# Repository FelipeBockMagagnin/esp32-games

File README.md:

# dotcompany Games

Every game for the dotcompany board (ESP32, 240x320 ILI9341, five buttons, a buzzer), the menu
that switches between them, the board's PCB and case, and the site that installs them over USB
from the browser (Chrome or Edge, through Web Serial and
[ESP Web Tools](https://esphome.github.io/esp-web-tools/)), served by GitHub Pages from `docs/`.

```
games/<id>/       one PlatformIO project per game, plus its game.json and screen.png
games/categories.json   the site's shelves, in page order
launcher/         the menu that boots the chosen game when several share a board
lib/              the engine the games share: dotcore (buttons, backlight, saves, settings,
                  pitches.h, Launcher.h) and dotui (the UI elements)
common.ini        the board's PlatformIO config, read by every platformio.ini
hardware/         the carrier PCB and the printed case
docs/             the site
tools/            publish.py, make_mockups.py, make_brand.py
```

## Publish

```bash
tools/publish.py              # every game whose firmware changed since it was published
tools/publish.py idle pet     # just these (`launcher` for the menu)
tools/publish.py --all        # everything
tools/publish.py --list       # only the game list and the screens, building nothing
git add docs && git commit -m "publish firmware" && git push
```

A game's version is the last commit that touched its firmware (its `src/`, `include/`, `lib/`
and `platformio.ini`, plus the repo's `lib/` and `common.ini`), so editing a description or another game
rebuilds nothing. Each build starts from clean. The script refuses a game with uncommitted
changes, so a published version is always a commit, and one with git-ignored files under `src/`
or `include/` (the Pomodoro's `secrets.h` holds a WiFi password, which must never reach a public
firmware). It writes `docs/firmware/<id>/` (the four images, the manifest, the launcher's icon)
and `docs/games.js`, and drops what is left of a game whose folder is gone.

The images keep their own offsets (bootloader 0x1000, partitions 0x8000, boot_app0 0xE000,
app 0x10000) instead of one merged image, whose 0xFF padding would cover NVS at 0x9000 and
erase every game's save. Every game must keep the default partition table for that to hold.

## Add a game

1. Copy the closest game to `games/<id>/`. The folder name is the id the site and the launcher use.
2. Give it its own NVS namespace, and make its reset clear only that namespace.
3. Write `game.json`:
   - `name`, `tagline`, `category` (an `id` from `games/categories.json`), `description` and `accent`;
   - optionally `order` (its place on the page and in the menu; unset goes last), `env`
     (default `esp32dev`) and `icon` (`[x, y, factor]`: the 64x64 icon the launcher and the site
     show is a crop of the screen, `64 * factor` wide).
4. Add a 240x320 `screen.png` (`tools/make_mockups.py` draws the existing games').
5. Commit, then run `tools/publish.py`. The site picks the game up from its folder.

## The console

The console on the page is the printed case: its proportions, window and D-pad come from
`hardware/case/case.scad`, measured in `--mm` (5.5556px, so the display's 43.2mm come out at its
240 pixels). `tools/make_brand.py` draws the engraved wordmark, the back's character and the
favicons from `hardware/case/brand.scad`. Rerun it if the case art changes.

## Preview

```bash
python3 -m http.server -d docs 8000   # http://localhost:8000, a secure context like HTTPS
```

## GitHub Pages

Settings → Pages → Deploy from a branch → `main`, folder `/docs`.

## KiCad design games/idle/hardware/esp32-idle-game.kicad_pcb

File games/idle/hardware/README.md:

# Placa do ESP32 Idle Game (v5)

Placa portátil de **62×100 mm**, 2 camadas, só com componentes PTH (fáceis de soldar à mão). Cabe na faixa mais barata da JLCPCB (US$ 2 por 5 placas).

- **Frente:** display de 2.8" no alto e a cruz de botões embaixo. OK fica no meio, UP em cima, DOWN embaixo, LEFT (tela anterior) à esquerda e RIGHT (próxima tela) à direita.
- **Verso:** a ESP32 deitada atrás do display, com o USB saindo pela lateral esquerda (vista de frente). Logo abaixo dela ficam o buzzer, R1, Q1, D1 e C1.

**O display de 2.8" não cabe inteiro numa placa de 100 mm** acima dos botões. Por isso o conector dele fica na borda de baixo do módulo, logo acima da cruz, e os ~17 mm de cima passam da borda da placa, apoiados em trilhos da case. Assim a PCB continua na faixa de US$ 2.

**O display e a ESP32 vão soldados direto na placa**, sem soquete. Isso deixa a case com **23 mm** de espessura, mas para tirar um deles depois é preciso dessoldar.

| Frente | Verso (visto por trás) |
|---|---|
|  |  |

## Arquivos

- `fab/esp32-idle-game-gerbers.zip`: o arquivo que se envia para a fábrica.
- `esp32-idle-game.kicad_pcb`: a placa, que abre no KiCad 10.
- `bom.csv`: lista de componentes por referência.
- `generate_pcb.py` e `build.sh`: geram tudo do zero (posicionamento, roteamento com Freerouting, plano de terra, DRC, Gerbers e prévias). Mudanças se fazem no `.py`, não no KiCad.
- `viewer.html`: visualização 3D de como display, ESP32, peças, parafusos e case se encaixam, com vista explodida, corte e checagem de folgas. Abre direto no navegador (precisa de internet para carregar o Three.js). O `build.sh` atualiza os dados dela via `viewer.py`.
- `case/`: a case impressa em 3D (seção 7).

```bash
hardware/build.sh ~/Downloads/freerouting-2.5.0.jar   # requer kicad 10 e java
```

## 1. Fabricar a PCB

**JLCPCB:** https://cart.jlcpcb.com/quote

1. Clique em **Add gerber file** e envie `fab/esp32-idle-game-gerbers.zip`. O tamanho de 62×100 mm é lido sozinho.
2. Deixe o padrão: FR-4, **2 layers**, **5 unidades**, espessura 1.6 mm, HASL. A cor verde é a mais barata e a mais rápida.
3. Não marque **PCB Assembly**: a montagem é manual.
4. No frete, escolha o mais barato que tenha rastreio (Global Standard Direct ou similar).

A JLCPCB imprime um número de pedido na serigrafia. Para tirar, escolha "Remove Mark" (custa um pouco a mais).

Alternativas: **PCBWay** (https://www.pcbway.com/orderonline.aspx), com as mesmas opções, ou a **PCB Brasil** (https://pcbbrasil.com.br/prototipos), que fabrica aqui e não paga importação.

A placa chega em 1 a 3 semanas. A importação de PCB paga imposto de importação mais ICMS sobre placa e frete.

## 2. Lista de compras (uma unidade)

Duas listas com tudo o que entra numa unidade montada: uma comprando só no Brasil, outra só no exterior. Os preços são estimativas de out/2026, com dólar a R$ 5,50. Os links levam a buscas ou a produtos de referência; confira as medidas no anúncio antes de comprar.

### Comprando no Brasil

| Qtd | Item | Onde | ~R$ |
|---|---|---|---|
| 1 | ESP32 DevKit V1, **30 pinos** | [Mercado Livre](https://lista.mercadolivre.com.br/esp32-30-pinos) | 33 – 60 |
| 1 | Display TFT **2.8"** ILI9341 SPI (14 pinos, com ou sem touch) | [Mercado Livre](https://lista.mercadolivre.com.br/display-tft-ili9341) | 64 – 93 |
| 5 | Chave táctil 6×6×5 mm (vendida por unidade) | [Eletrogate](https://www.eletrogate.com/push-button-chave-tactil-6x6x5mm) | 0,75 |
| 1 | Buzzer passivo **12 mm**, 5 V (12×10 mm; pernas a 6,5 ou 7,6 mm) | [Eletrogate](https://www.eletrogate.com/buzzer-passivo-5v) | 1,90 |
| 1 | Transistor S8050 ou 2N2222A, **ou BC337 girado** (veja abaixo) | [Mercado Livre](https://lista.mercadolivre.com.br/transistor-s8050) · [Eletrogate BC337](https://www.eletrogate.com/transistor-npn-bc337) | 0,30 – 1 |
| 1 pct | Diodo 1N4148 (10 un.) | [Eletrogate](https://www.eletrogate.com/diodo-1n4148) | 1,40 |
| 1 pct | Resistor 1 kΩ 1/4 W (10 un.) | [Eletrogate](https://www.eletrogate.com/resistor-1k-1-4w-10-unidades) | 0,70 |
| 1 | Capacitor eletrolítico 100 µF, 16 ou 25 V | [Eletrogate (25 V)](https://www.eletrogate.com/capacitor-eletrolitico-100uf-x-25v) | 0,30 |
| 4 | Parafuso M3×6 | [Mercado Livre](https://lista.mercadolivre.com.br/parafuso-m3x6) | 2 – 5 |
| *opc.* | Fita kapton, se o slot SD do display encostar nos pinos do J2 | [Mercado Livre](https://lista.mercadolivre.com.br/fita-kapton) | 8 – 15 |
| *opc.* | Capacitor 10 µF 16 V, se a gravação falhar com a case fechada (entre EN e GND) | [Eletrogate](https://www.eletrogate.com/capacitor-eletrolitico-10uf-x-16v) | 0,20 |
| 1 | PCB 62×100 mm, 2 camadas (lote de 5) | [PCB Brasil](https://pcbbrasil.com.br/prototipos) (cotação online com o zip) | a cotar |
| ~50 g | Filamento PLA para a case | Se já tiver impressora | 5 – 8 |
| — | Frete de 2 a 3 lojas | | 30 – 60 |
| | **Total, sem a PCB** | | **~140 – 230 (típico ~165)** |

O display de 2.8" é fácil de achar no Brasil, o que deixa a compra nacional mais em conta do que com a tela de 2.2".

**Na Eletrogate** (estoque conferido em 07/10/2026) dá para comprar os componentes pequenos e o buzzer, mas não os módulos:

- **ESP32:** a de 30 pinos está esgotada, e a página informa 25,5 mm de largura, o que sugere fileiras a 22,86 mm, que não encaixam.
- **Display:** não vendem o 2.8" SPI.

**BC337 no lugar do S8050:** o S8050 e o 2N2222 estavam esgotados. O BC337 serve, mas a ordem das pernas dele é C-B-E, invertida em relação à placa. Monte-o **girado 180°**, com a face plana para o lado oposto ao desenho da serigrafia, para que cada perna caia no furo E, B ou C certo.

Não encontrei preço publicado da PCB Brasil. Para comparar, envie `fab/esp32-idle-game-gerbers.zip` na cotação. Se der menos de uns R$ 140 pelas 5 placas entregues, sai mais barato que a JLCPCB.

### Comprando no exterior (AliExpress + JLCPCB)

| Qtd | Item | Busca | ~US$ |
|---|---|---|---|
| 1 | ESP32 DevKit V1, **30 pinos** | [AliExpress](https://www.aliexpress.com/w/wholesale-esp32-devkit-v1-30pin.html) | 3 |
| 1 | Display TFT **2.8"** ILI9341 SPI (14 pinos, 50×86 mm) | [AliExpress](https://www.aliexpress.com/w/wholesale-2.8-tft-lcd-ili9341.html) | 6 |
| 1 pct | Chave táctil 6×6×5 mm | [AliExpress](https://www.aliexpress.com/w/wholesale-tactile-switch-6x6x5mm.html) | 1 |
| 1 pct | Buzzer passivo 12 mm, 5 V (12×9,5 ou 12×10 mm) | [AliExpress](https://www.aliexpress.com/w/wholesale-passive-buzzer-12mm-5v.html) | 1 |
| 1 pct | Transistor S8050, TO-92 | [AliExpress](https://www.aliexpress.com/w/wholesale-s8050-to-92-transistor.html) | 1 |
| 1 pct | Diodo 1N4148 | [AliExpress](https://www.aliexpress.com/w/wholesale-1n4148-diode.html) | 0,5 |
| 1 pct | Resistor 1 kΩ 1/4 W | [AliExpress](https://www.aliexpress.com/w/wholesale-resistor-1k-1%2F4w.html) | 0,5 |
| 1 pct | Capacitor eletrolítico 100 µF 16 V, 5×11 mm | [AliExpress](https://www.aliexpress.com/w/wholesale-electrolytic-capacitor-100uf-16v-5x11.html) | 0,5 |
| 1 pct | Parafuso M3×6 | [AliExpress](https://www.aliexpress.com/w/wholesale-m3x6-screw.html) | 1 |
| | AliExpress, subtotal | | 14,50 |
| | + ICMS (pedido até US$ 50, Remessa Conforme) | | ≈ 18,10 → **R$ 100** |
| 5 | PCB 62×100 mm (JLCPCB), US$ 2 + frete Global Standard ~US$ 11 | [JLCPCB](https://cart.jlcpcb.com/quote) | 13 |
| | + imposto de importação 60% e ICMS | | ≈ 26 → **R$ 143** |
| ~50 g | Filamento PLA para a case | | R$ 5 – 8 |
| | **Total** | | **~R$ 250** |

No exterior, os pacotes de peças pequenas e as 4 PCBs que sobram já dão para montar mais unidades. A segunda unidade custa só a ESP32 e o display, uns R$ 60 a mais.

### Qual compensa

- **Uma unidade:** no Brasil, as peças dão uns R$ 165 com frete, mais a cotação da PCB Brasil. No exterior, sai tudo por uns R$ 250, com 3 a 6 semanas de espera. Para uma unidade, comprar as peças aqui costuma ganhar.
- **Duas ou mais unidades:** o exterior ganha. As peças são muito mais baratas e a PCB já vem em lote de 5.

## 3. Ferramentas

- Ferro de solda (ponta fina, ~330 °C) e estanho 0,8 mm com fluxo
- **Alicate de corte rente** (indispensável: vários terminais precisam ficar rentes à placa)
- Multímetro (para o teste de continuidade)
- Fita crepe ou massinha, para segurar as peças enquanto solda

## 4. Montagem

A regra geral: **cada peça entra pelo lado em que fica e é soldada pelo lado oposto.**

O display fica a só 2,5 mm da frente da placa, e a ESP32 a 2,5 mm do verso. Por isso, **todo terminal soldado embaixo deles precisa ser cortado rente**, a menos de 1 mm. E a ordem importa: a ESP32 vem antes do display, porque a solda dela fica escondida embaixo do display.

### Antes de começar: confira
1. **Ordem dos pinos do display.** Acima do J1, na frente da placa, estão impressos os nomes dos 14 pinos (VCC, GND, CS… T_IRQ). Com o display de face para cima e o conector embaixo, o VCC fica à **esquerda** (conferido num módulo real). Compare com a marcação do seu módulo. Se estiver espelhado, **não solde**: troque o lado do pino 1 do J1 no `generate_pcb.py` (`display_left` e o ângulo do footprint) e gere a placa de novo.
2. **Largura da ESP32.** Meça a distância entre as duas fileiras de pinos, centro a centro. Precisa dar 25,4 mm.
3. **A ESP32 funciona?** Ligue-a no USB e grave o jogo (seção 6) antes de soldar. Depois de soldada, trocar dá trabalho.

### Verso (lado azul na prévia): componentes abaixo da ESP32
4. **R1 (1 kΩ):** dobre as pernas, encaixe pelo verso e solde pela frente. Não tem polaridade.
5. **D1 (1N4148):** a faixa preta do diodo vai do lado marcado **K**.
6. **Q1 (S8050):** as pernas seguem as letras **E B C** impressas. Empurre até o corpo ficar a ~1 mm da placa. Um BC337 (pernas C-B-E) entra girado 180°, com a face plana para o lado oposto ao desenho.
7. **Buzzer:** a perna **+** vai no pad quadrado (marcado com +). Os furos são oblongos: servem para pernas a 6,5 ou 7,6 mm. Encostado na placa. Com 10 mm de altura, é a peça mais baixa do verso: a case fica 1 mm abaixo dele.
8. **C1 (100 µF):** a perna longa (+) vai no pad marcado com **+**. Dobre as pernas a 90° rente ao corpo e deite o capacitor sobre o retângulo "C1" impresso, na direção dos botões.
9. Corte rente, na frente, as pernas de todos eles: essa área fica embaixo do display.

### Frente (lado vermelho na prévia)
10. **Botões:** os cinco encaixam por pressão. Solde as 4 pernas de cada um, conferindo se ficaram rentes à placa.

### Teste antes dos módulos
11. Com o multímetro em continuidade, meça entre os pads **VIN** e **GND** do J3 (verso). **Não pode apitar.** Se apitar, há um curto: procure uma ponte de solda.
12. Aperte cada botão e meça entre o pad dele no J2/J3 (D19, D22, D27, D26 e D23) e o GND. Deve apitar só enquanto o botão estiver apertado.

### ESP32 (verso)
13. Encaixe os pinos da ESP32 pelo **verso**, deitada, **com os componentes virados para fora e o USB voltado para a borda esquerda** (vista pela frente; pelo verso, fica à direita, onde está escrito "USB"). O espaçador plástico dos pinos deve encostar na placa.
14. Solde pela frente: primeiro um pino de cada ponta, confira se ficou reta, depois o resto.
15. **Corte rente todos os 30 pinos na frente.** Eles ficam embaixo do display.

### Display (frente)
16. Encaixe os 14 pinos do display pela **frente**, de face para cima e **com o conector embaixo**, perto dos botões. O espaçador plástico deve encostar na placa, e o resto do módulo passa da borda de cima.
17. Solde pelo verso, logo acima dos botões, e corte as pontas. Até a placa entrar na case, segure o display com cuidado: a parte que passa da placa fica sem apoio.

### Acabamento
18. Monte na case (seção 7) ou, sem case, parafuse 4 espaçadores M3 de 12 mm no verso como pés.

## 5. Primeiro teste

Ligue o USB. O LED vermelho da ESP32 deve acender, o display deve mostrar o jogo e o buzzer deve tocar ao apertar RIGHT.

Se a tela ficar branca, confira as soldas do display. Se nada acender, desligue e refaça o teste de VIN e GND.

## 6. Gravar o jogo

Com a ESP32 conectada ao computador:

```bash
~/.platformio/penv/bin/pio run -t upload
```

O display de 2.8" usa o mesmo controlador (ILI9341) e a mesma resolução, então a configuração não muda. Como o conector fica embaixo, a imagem pode aparecer de cabeça para baixo: troque `tft.setRotation(2)` por `tft.setRotation(0)` em `src/main.cpp`, ou o contrário. Dá para gravar de novo a qualquer momento, com tudo já montado, pelo USB na lateral esquerda da case.

## 7. Case impressa em 3D

Os arquivos estão em `case/`: o modelo paramétrico `case.scad` (OpenSCAD) os STLs prontos para fatiar (as três peças e as partes coloridas da logo) e o `case.3mf`, que junta tudo num arquivo só para mandar imprimir. `brand.scad` guarda a arte da dotcompany em pixels, tirada de `src/assets/png/sprites/splash/`.

| Arquivo | Peça | Como imprimir |
|---|---|---|
| `case_bottom.stl` | Bandeja: a PCB é parafusada nela; a ESP32 e o buzzer ficam dentro, com o fundo fechado. Leva o personagem e o nome da dotcompany gravados por fora | Fundo na mesa |
| `case_top.stl` | Moldura com a janela do display e os furos da cruz, com DOTCOMPANY gravado acima da tela | **De cabeça para baixo** (face externa na mesa) |
| `case_caps.stl` | 5 botões, que levam o toque da tampa até as chaves | Base na mesa |

**Impressão:** PLA ou PETG, camada de 0,2 mm, 3 perímetros, 20% de preenchimento. Nenhuma peça precisa de suporte. As medidas externas ficam em 67×122×23 mm. O fundo é fechado: o som do buzzer sai pela abertura do USB e pelos furos dos botões.

**Logo:** a arte fica gravada 0,6 mm (3 camadas) na face que vai na mesa, então sai sem suporte. Ela tem **três cores**, como o personagem original: capuz, corpo e nomes em preto, o rosto em cinza, e a máscara na cor da própria case (por isso a case fica branca ou cinza bem claro).

- **Impressora multicor** (AMS, MMU, com 3 filamentos): `case_top_logo.stl`, `case_bottom_logo.stl` (preto) e `case_bottom_face.stl` (cinza) preenchem o baixo-relevo. No fatiador, carregue cada peça junto com as partes dela como **um objeto com várias partes** (o fatiador pergunta), para que mantenham a posição. Só as 3 primeiras camadas têm mais de uma cor, então a purga gasta pouco.
- **Um bico só:** trocar o filamento numa camada não funciona, porque a logo divide as mesmas camadas com o resto da face. Pinte o baixo-relevo com tinta acrílica ou esmalte (rosto cinza, o resto preto) e raspe o excesso com uma espátula.

**Mandar imprimir:** envie só o `case.3mf`. Ele tem as três peças numa mesa só (208×122 mm), já viradas do jeito certo de imprimir, e as partes da logo encaixadas nas suas peças, cada uma com sua cor. Mande junto as instruções, porque nem todo fatiador lê a cor do arquivo:

> Case em 3 peças + botões, tudo no `case.3mf`, já orientado; não precisa de suporte. PLA ou PETG, camada 0,2 mm, 3 perímetros, 20% de preenchimento. Três cores: peças em **branco** (ou cinza bem claro), as partes "Bandeja logo" e "Moldura logo" em **preto** e a parte "Bandeja rosto" em **cinza médio**. As partes coloridas já estão encaixadas nas peças e ocupam só as 3 primeiras camadas (0,6 mm).

Se o serviço só imprimir em uma cor, a logo sai gravada do mesmo jeito; aí peça para ignorar as partes coloridas e pinte depois. Se pedirem STL, mande os seis `case_*.stl` e avise que as partes coloridas têm que ficar na posição original da peça delas.

**Montagem:**
1. Comece com a placa já montada (ESP32 e display soldados).
2. Coloque a placa na bandeja, com o USB alinhado à abertura da parede esquerda e o display apoiado nos dois trilhos da parte de cima. Prenda com os 4 parafusos M3×6 pela frente. Os furos de 2,6 mm são para o parafuso abrir rosca no plástico; não aperte demais.
3. Ponha os 5 botões impressos nos furos da moldura, por dentro, com a base larga virada para dentro.
4. Segurando os botões, encaixe a moldura na bandeja até ouvir o clique dos dois lados. Para abrir, use o entalhe na lateral direita.

**Se não encaixar direito**, ajuste no topo do `case.scad` e exporte de novo:
- `switch_h`: altura da sua chave táctil, da placa ao topo do botão. O padrão é 5 mm (6×6×5). Se os botões impressos ficarem frouxos ou duros, o problema é este valor.
- `cap_d`: diâmetro visível dos botões (8,5 mm, o máximo para o espaçamento de 10,5 mm da placa). Diminua se preferir mais plástico entre os furos.
- `display_thick`: espessura do módulo do display (placa + vidro). O padrão é 4,5 mm.
- `window` e `display_center`: tamanho e posição da janela, caso a área visível do seu display fique deslocada.
- `fit`: folga do encaixe da moldura. Aumente para 0,25 se ficar justo demais.
- `brand_depth`, `word_px`, `char_px`: profundidade da gravação e tamanho de cada pixel do nome e do personagem. Abaixo de 0,6 mm em `word_px`, os vãos de 1 pixel das letras ficam mais finos que o bico e somem.

```bash
openscad -D 'part="bottom"' -o case_bottom.stl case.scad   # também: top, caps, top_logo, bottom_logo, bottom_face
python3 export_3mf.py                                        # junta os STLs no case.3mf
```

## Ligações (referência)

| ESP32 | Vai para |
|---|---|
| VIN (5 V do USB) | Display VCC, buzzer +, C1 |
| EN | Display RESET (por isso `TFT_RST=-1`) |
| GPIO 15 / 2 / 13 / 14 / 12 | Display CS / DC / MOSI / SCK / MISO |
| GPIO 21 | Display LED (backlight) |
| GPIO 19 / 22 / 27 / 26 / 23 | Botões UP / DOWN / OK / LEFT / RIGHT (pull-up interno, fecham para GND) |
| GPIO 32 | R1 1k → base do Q1. Q1 aciona o buzzer em 5 V, com D1 de roda-livre |

Se mudar um pino no código, mude também em `ESP_NETS` no `generate_pcb.py` e gere a placa de novo.

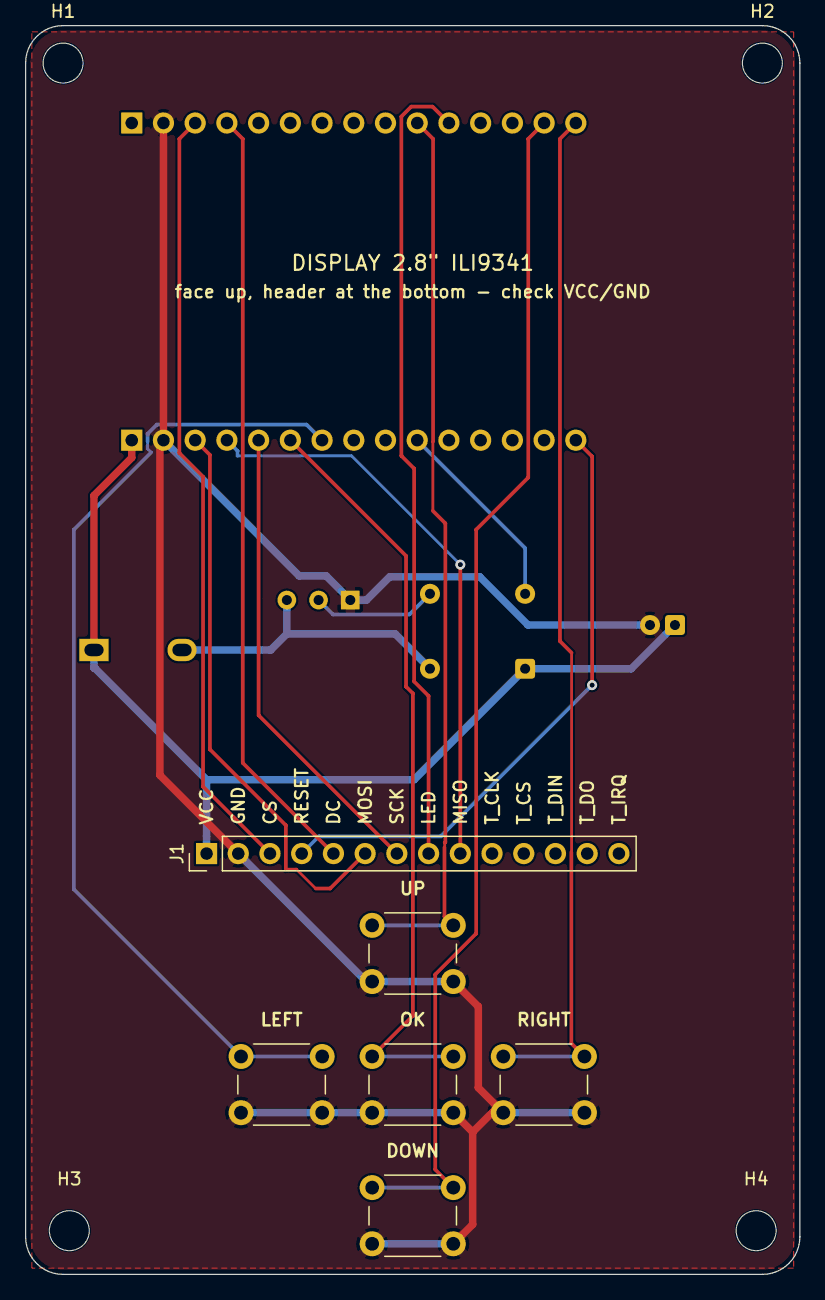
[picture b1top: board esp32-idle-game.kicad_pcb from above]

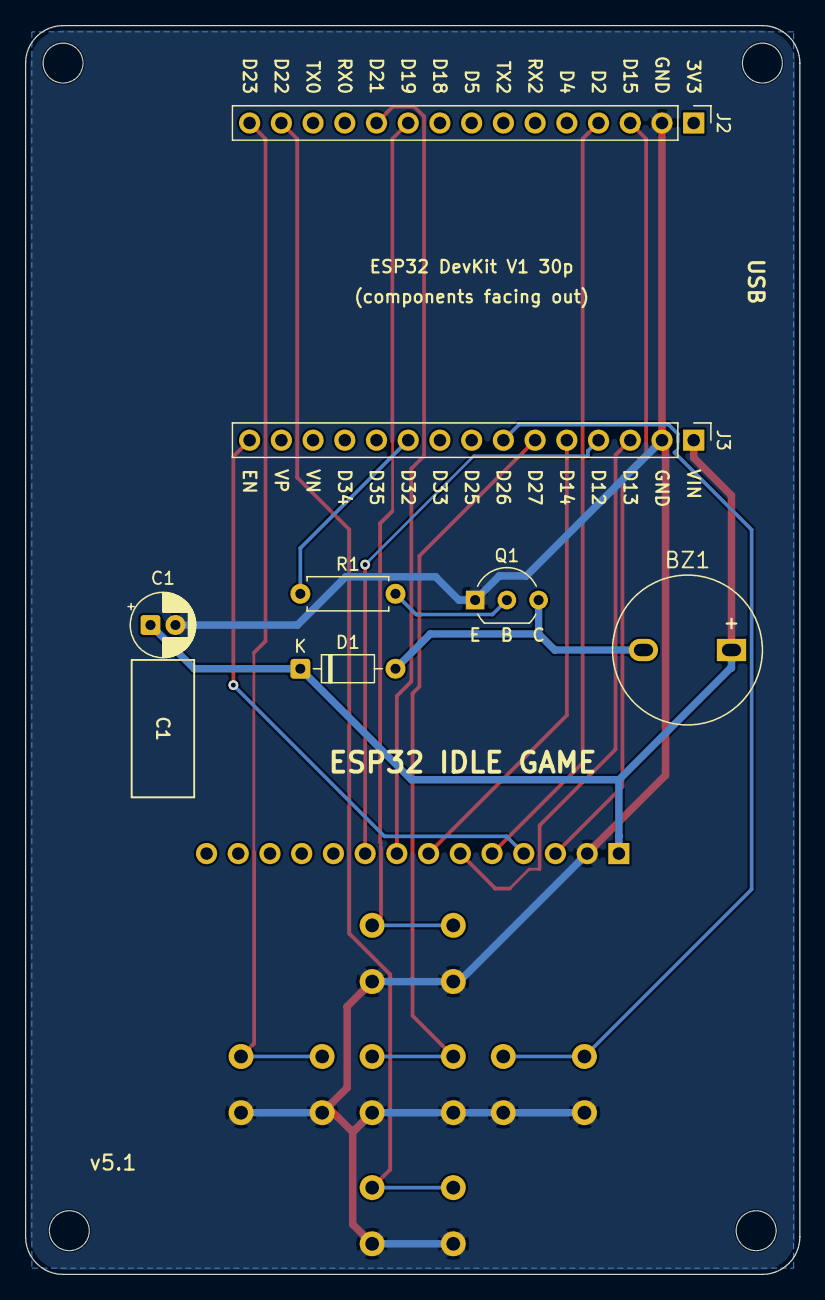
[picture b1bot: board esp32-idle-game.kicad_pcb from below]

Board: 2 copper layers, 62.0 x 100.0 mm, 17 parts (7 on the bottom side), 17 nets.

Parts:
BZ1: Passive buzzer 12mm; Buzzer_D12mm_P6.5-7.6mm
C1: 100uF 16V; CP_Radial_D5.0mm_P2.00mm
D1: 1N4148; D_DO-35_SOD27_P7.62mm_Horizontal
H1, H2, H3, H4: M3; MountingHole_3.2mm_M3
J1: ILI9341 2.8in; PinHeader_1x14_P2.54mm_Vertical
J2, J3: ESP32 DevKit V1; PinHeader_1x15_P2.54mm_Vertical
Q1: S8050 (EBC); TO-92_Inline_Wide
R1: 1k; R_Axial_DIN0207_L6.3mm_D2.5mm_P7.62mm_Horizontal
SW1, SW2, SW3, SW4, SW5: 6x6 tact; SW_PUSH_6mm

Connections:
+5V: BZ1.1, C1.1, D1.1, J1.1, J3.1
BTN_CONFIRM: J3.6, SW3.1
BTN_DOWN: J2.14, SW2.1
BTN_LEFT: J3.7, SW4.1
BTN_RIGHT: J2.15, SW5.1
BTN_UP: J2.10, SW1.1
BUZZER: J3.10, R1.1
BUZ_B: Q1.2, R1.2
BUZ_N: BZ1.2, D1.2, Q1.3
EN: J1.4, J3.15
GND: C1.2, J1.2, J2.2, J3.2, Q1.1, SW1.2, SW2.2, SW3.2, SW4.2, SW5.2
TFT_CS: J1.3, J2.3
TFT_DC: J1.5, J2.4
TFT_LED: J1.8, J2.11
TFT_MISO: J1.9, J3.4
TFT_MOSI: J1.6, J3.3
TFT_SCK: J1.7, J3.5
